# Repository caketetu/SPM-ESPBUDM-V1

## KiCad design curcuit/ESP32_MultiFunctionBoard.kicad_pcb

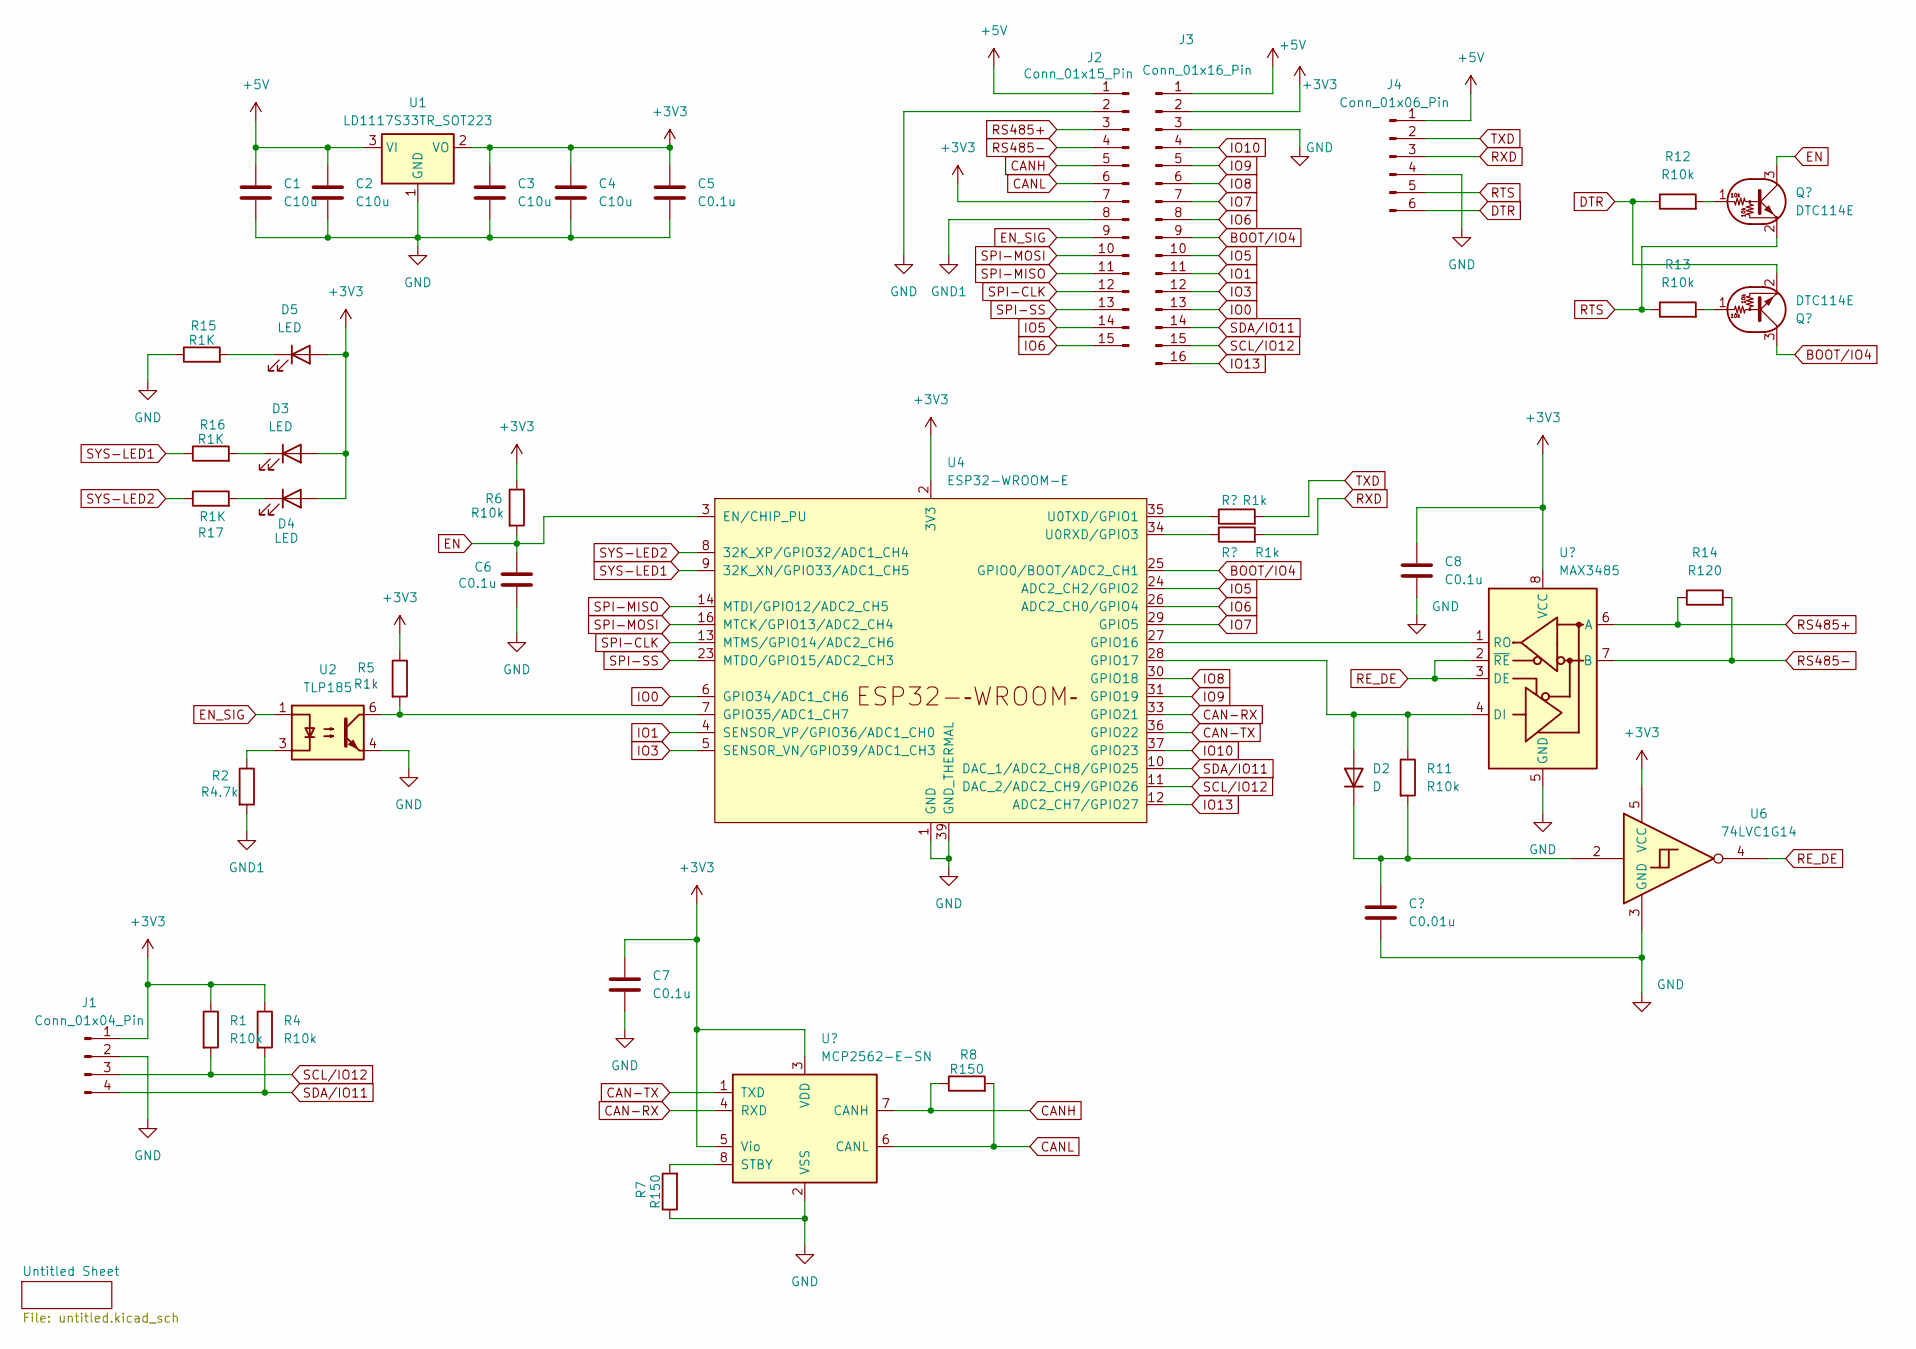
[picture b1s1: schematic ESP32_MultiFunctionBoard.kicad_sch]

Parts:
C1, C2, C3, C4: C10u; C_1206_3216Metric
C5, C6, C7, C8: C0.1u; C_0603_1608Metric
C9: C0.01u; C_0805_2012Metric
D2: D; D_1206_3216Metric
D3, D4, D5: LED; LED_0603_1608Metric
J1: Conn_01x04_Pin; PinSocket_1x04_P2.54mm_Vertical
J2: Conn_01x15_Pin; PinHeader_1x15_P2.54mm_Vertical
J3: Conn_01x16_Pin; PinSocket_1x16_P2.54mm_Vertical
J4: Conn_01x06_Pin; JST_ZH_B6B-ZR_1x06_P1.50mm_Vertical
Q1, Q2: DTC114E; SOT-23
R1, R4, R6, R11, R12, R13: R10k; R_0603_1608Metric
R2: R4.7k; R_0603_1608Metric
R5, R9, R10: R1k; R_0603_1608Metric
R7: R150; R_0603_1608Metric
R8: R150; R_1206_3216Metric
R14: R120; R_1206_3216Metric
R15, R16, R17: R1K; R_0603_1608Metric
U1: LD1117S33TR_SOT223; SOT-223-3_TabPin2
U2: TLP185; SOIC-4_4.55x3.7mm_P2.54mm
U3: MCP2562-E-SN; SOIC-8_3.9x4.9mm_P1.27mm
U4: ESP32-WROOM-E; ESP32-WROOM-32E
U5: MAX3485; SOIC-8_3.9x4.9mm_P1.27mm
U6: 74LVC1G14; SOT-23-5

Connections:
+3V3: C3.1, C4.1, C5.1, C7.1, C8.1, D3.2 (A), D4.2 (A), D5.2 (A), J1.1, J2.7, J3.2, R1.1, R4.1, R5.1, R6.1, U1.2 (VO), U3.3 (VDD), U3.5 (Vio), U4.2 (3V3), U5.8 (VCC), U6.5 (VCC); also elsewhere on the board
+5V: C1.1, C2.1, J2.1, J3.1, J4.1, U1.3 (VI); also elsewhere on the board
BOOT/IO4: J3.9, Q2.3 (C), U4.25 (GPIO0/BOOT/ADC2_CH1); also elsewhere on the board
CAN-RX: U3.4 (RXD), U4.33 (GPIO21)
CAN-TX: U3.1 (TXD), U4.36 (GPIO22)
CANH: J2.5, R8.1, U3.7 (CANH)
CANL: J2.6, R8.2, U3.6 (CANL)
DTR: J4.6, Q2.2 (E), R12.1
EN: C6.1, Q1.3 (C), R6.2, U4.3 (EN/CHIP_PU)
EN_SIG: J2.9, U2.1
GND: C1.2, C2.2, C3.2, C4.2, C5.2, C6.2, C7.2, C8.2, C9.2, J1.2, J2.2, J3.3, J4.4, R7.1, R15.1, U1.1 (GND), U2.4, U3.2 (VSS), U4.1 (GND), U4.15 (GND), U4.38 (GND), U4.39 (GND_THERMAL), U5.5 (GND), U6.3 (GND); also elsewhere on the board
GND1: J2.8, R2.2
IO0: J3.13, U4.6 (GPIO34/ADC1_CH6); also elsewhere on the board
IO1: J3.11, U4.4 (SENSOR_VP/GPIO36/ADC1_CH0); also elsewhere on the board
IO3: J3.12, U4.5 (SENSOR_VN/GPIO39/ADC1_CH3); also elsewhere on the board
IO5: J2.14, J3.10, U4.24 (ADC2_CH2/GPIO2); also elsewhere on the board
IO6: J2.15, J3.8, U4.26 (ADC2_CH0/GPIO4); also elsewhere on the board
IO7: J3.7, U4.29 (GPIO5); also elsewhere on the board
IO8: J3.6, U4.30 (GPIO18); also elsewhere on the board
IO9: J3.5, U4.31 (GPIO19); also elsewhere on the board
IO10: J3.4, U4.37 (GPIO23); also elsewhere on the board
IO13: J3.16, U4.12 (ADC2_CH7/GPIO27); also elsewhere on the board
unnamed: D2.2 (A), R11.1, U4.28 (GPIO17), U5.4 (DI)
unnamed: C9.1, D2.1 (K), R11.2, U6.2
unnamed: D3.1 (K), R16.2
unnamed: D4.1 (K), R17.2
unnamed: D5.1 (K), R15.2
unnamed: Q1.1 (B), R12.2
unnamed: Q2.1 (B), R13.2
unnamed: R2.1, U2.3
unnamed: R7.2, U3.8 (STBY)
unnamed: U4.27 (GPIO16), U5.1 (RO)
unnamed: R5.2, U2.6, U4.7 (GPIO35/ADC1_CH7)
unnamed: R10.1, U4.34 (U0RXD/GPIO3)
unnamed: R9.1, U4.35 (U0TXD/GPIO1)
RE_DE: U5.2 (~RE), U5.3 (DE), U6.4
RS485+: J2.3, R14.1, U5.6 (A)
RS485-: J2.4, R14.2, U5.7 (B)
RTS: J4.5, Q1.2 (E), R13.1
RXD: J4.3, R10.2
SCL/IO12: J1.3, J3.15, R1.2, U4.11 (DAC_2/ADC2_CH9/GPIO26); also elsewhere on the board
SDA/IO11: J1.4, J3.14, R4.2, U4.10 (DAC_1/ADC2_CH8/GPIO25); also elsewhere on the board
SPI-CLK: J2.12, U4.13 (MTMS/GPIO14/ADC2_CH6)
SPI-MISO: J2.11, U4.14 (MTDI/GPIO12/ADC2_CH5)
SPI-MOSI: J2.10, U4.16 (MTCK/GPIO13/ADC2_CH4)
SPI-SS: J2.13, U4.23 (MTDO/GPIO15/ADC2_CH3)
SYS-LED1: R16.1, U4.9 (32K_XN/GPIO33/ADC1_CH5)
SYS-LED2: R17.1, U4.8 (32K_XP/GPIO32/ADC1_CH4)
TXD: J4.2, R9.2

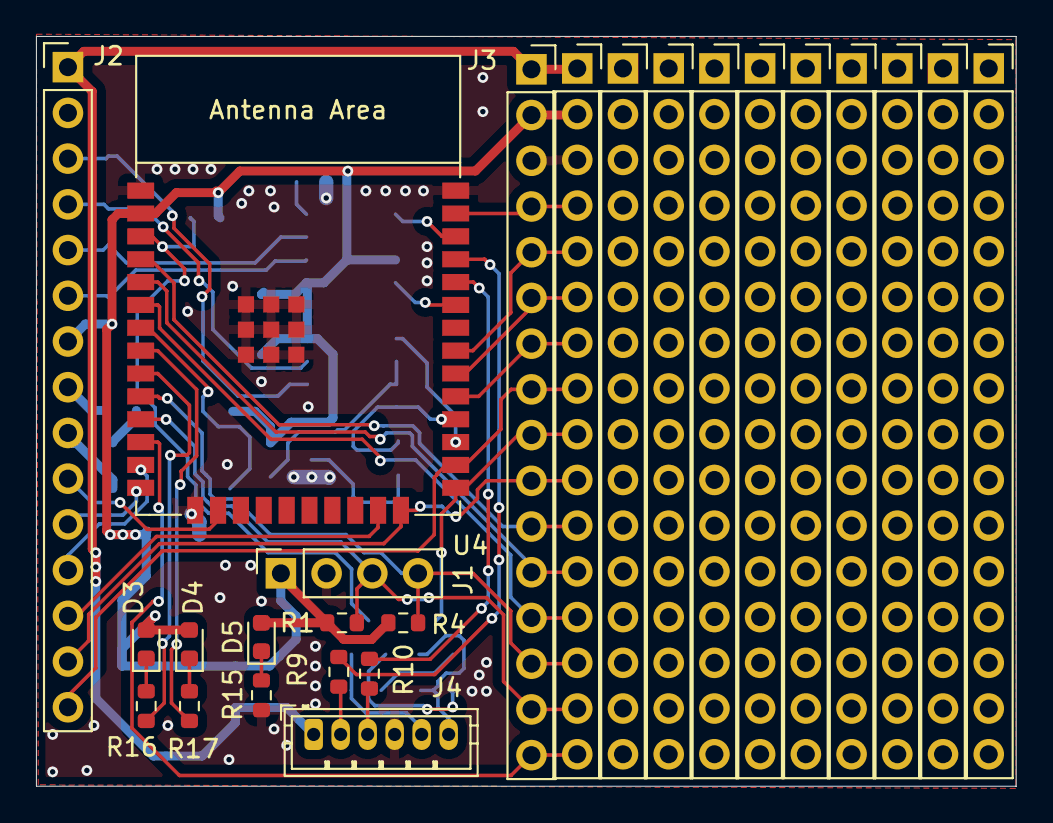
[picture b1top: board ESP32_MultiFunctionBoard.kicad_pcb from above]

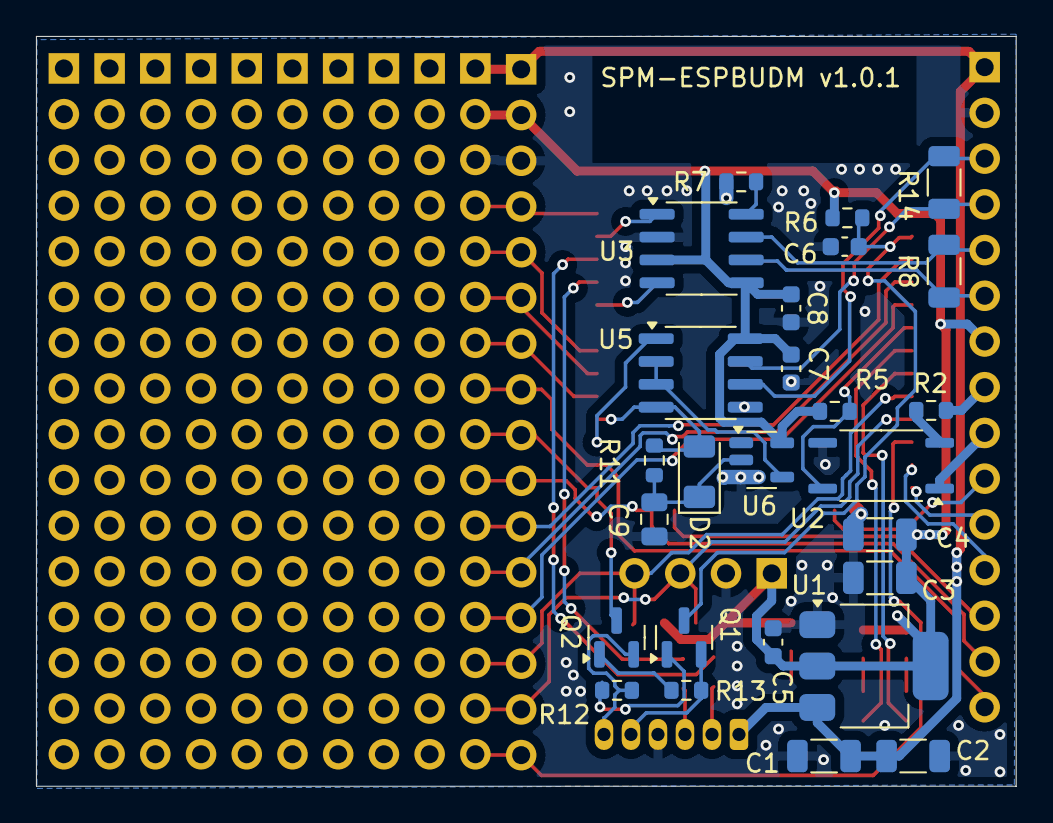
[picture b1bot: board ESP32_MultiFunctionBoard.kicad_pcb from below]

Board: 2 copper layers, 54.4 x 41.7 mm, 51 parts (26 on the bottom side), 49 nets.

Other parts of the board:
J5, J6, J7, J8, J9, J10, J11, J12, J13, J14: Conn_01x16_Pin; PinSocket_1x16_P2.54mm_Vertical

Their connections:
+3V3: J5.2; also elsewhere on the board
+5V: J5.1; also elsewhere on the board
BOOT/IO4: J5.9; also elsewhere on the board
GND: J5.3; also elsewhere on the board
IO0: J5.13; also elsewhere on the board
IO1: J5.11; also elsewhere on the board
IO3: J5.12; also elsewhere on the board
IO5: J5.10; also elsewhere on the board
IO6: J5.8; also elsewhere on the board
IO7: J5.7; also elsewhere on the board
IO8: J5.6; also elsewhere on the board
IO9: J5.5; also elsewhere on the board
IO10: J5.4; also elsewhere on the board
IO13: J5.16; also elsewhere on the board
SCL/IO12: J5.15; also elsewhere on the board
SDA/IO11: J5.14; also elsewhere on the board
